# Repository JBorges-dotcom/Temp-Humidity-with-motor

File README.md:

This is a basic project to circulate air inside of the greenhouse in my apartment to prevent mold and fungus flies. 
It uses an Arduino Nano to read a DHT11 temp/humidity sensor and display the readings to a 7-segment LCD. It also has a small DC motor to circulate the air by turning on and off every 15 minutes.

The board has dimensions 53.4mm x 61.5 mm.

Some photos of the initial prototype board:

Another with the lights off so it's easier to see the LCD screen. The first two numbers show the temperature in Fahrenheit, and the last two numbers show the humidity percentage.

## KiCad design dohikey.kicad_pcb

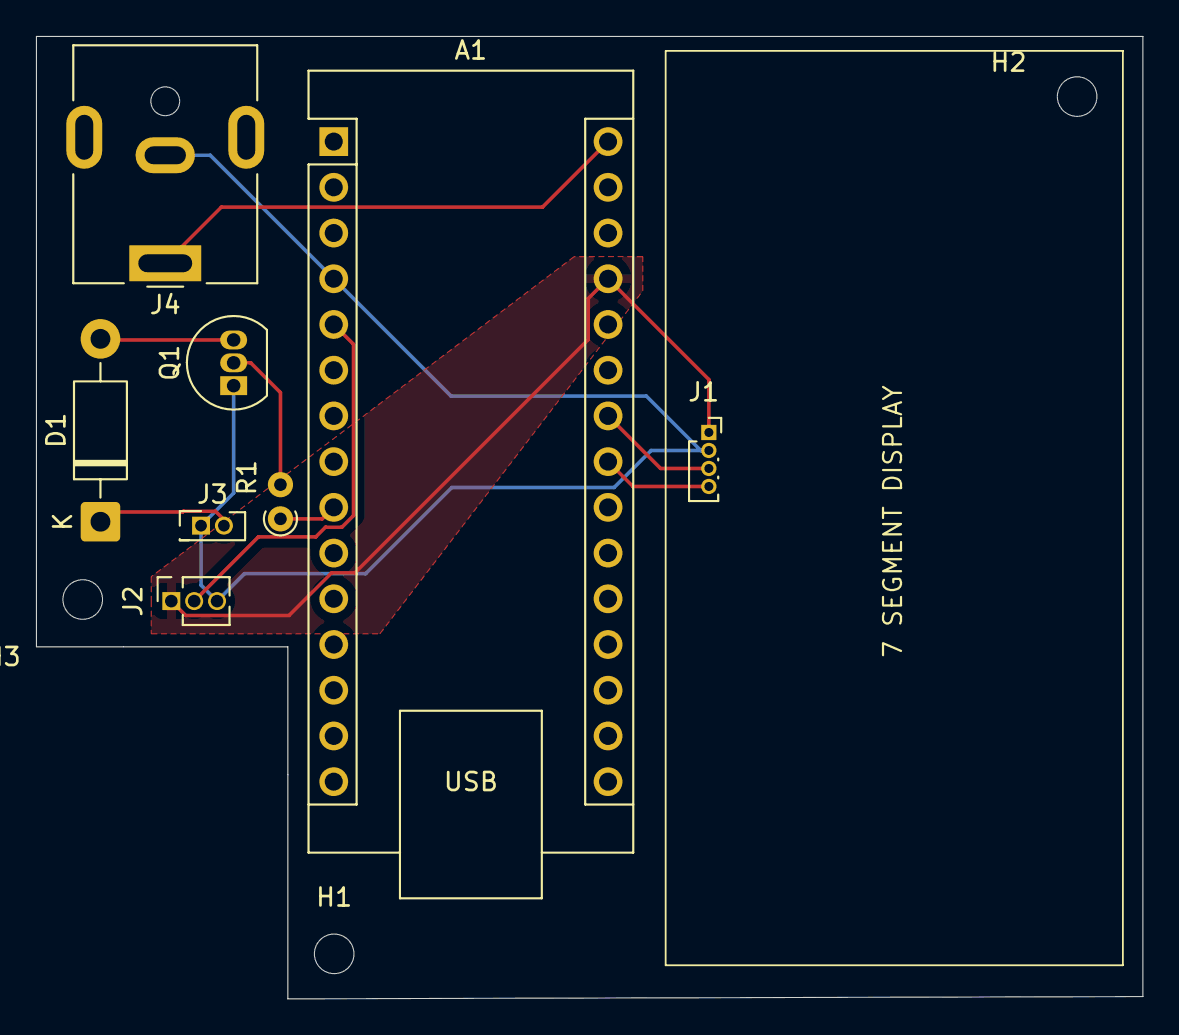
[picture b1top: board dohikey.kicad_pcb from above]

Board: 2 copper layers, 61.5 x 53.5 mm, 11 parts (0 on the bottom side), 10 nets.

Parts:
A1: Arduino_Nano_v3.x; Arduino_Nano
D1: 1N4001; D_DO-41_SOD81_P10.16mm_Horizontal
H1, H2, H3: MountingHole; MountingHole_2.2mm_M2
J1: Conn_01x04_Pin; PinSocket_1x04_P1.00mm_Vertical
J2: DHT11; PinSocket_1x03_P1.27mm_Vertical
J3: Motor; PinHeader_2x01_P1.27mm_Vertical
J4: Barrel_Jack_Switch_Pin3Ring; BarrelJack_CUI_PJ-063AH_Horizontal
Q1: PN2222A; TO-92_Inline
R1: 270; R_Axial_DIN0204_L3.6mm_D1.6mm_P1.90mm_Vertical

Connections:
+5V: A1.27 (+5V), J1.1, J2.1
GND: A1.4 (GND), J1.2, J2.3, J3.1, J4.2, Q1.1 (E)
unnamed: A1.23 (A4), J1.4
unnamed: A1.24 (A5), J1.3
unnamed: A1.5 (D2), J2.2
unnamed: A1.9 (D6), R1.1
unnamed: A1.30 (VIN), J4.1
unnamed: D1.2 (A), Q1.3 (C)
unnamed: D1.1 (K), J3.2
unnamed: Q1.2 (B), R1.2

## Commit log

2026-03-08 Delete dohikey-2026-03-07_202829.zip
    Remove old build files
